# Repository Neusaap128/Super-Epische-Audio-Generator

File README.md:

**CubeIDEProject:** Deze bevat de code die we op de dev board geschreven hebben voor we overschakelde naar de PCB \
**FiltersWavFiles:** Bevat de C-code en de wav files van filters \
**KicadProject:** De technische schema's van onze PCB en hoe we alles hebben aangesloten aan elkaar \
**SEAG_F:** De implementatie op de STM32F722RC (wat we uitendelijk gebruikt hebben) \
**Super Epische Audio Generator:** Bevat Datasheet per onderdeel, PCB benodigheden, Tekst documenten voor Seminarie waar ook het eindverslag van alles staat

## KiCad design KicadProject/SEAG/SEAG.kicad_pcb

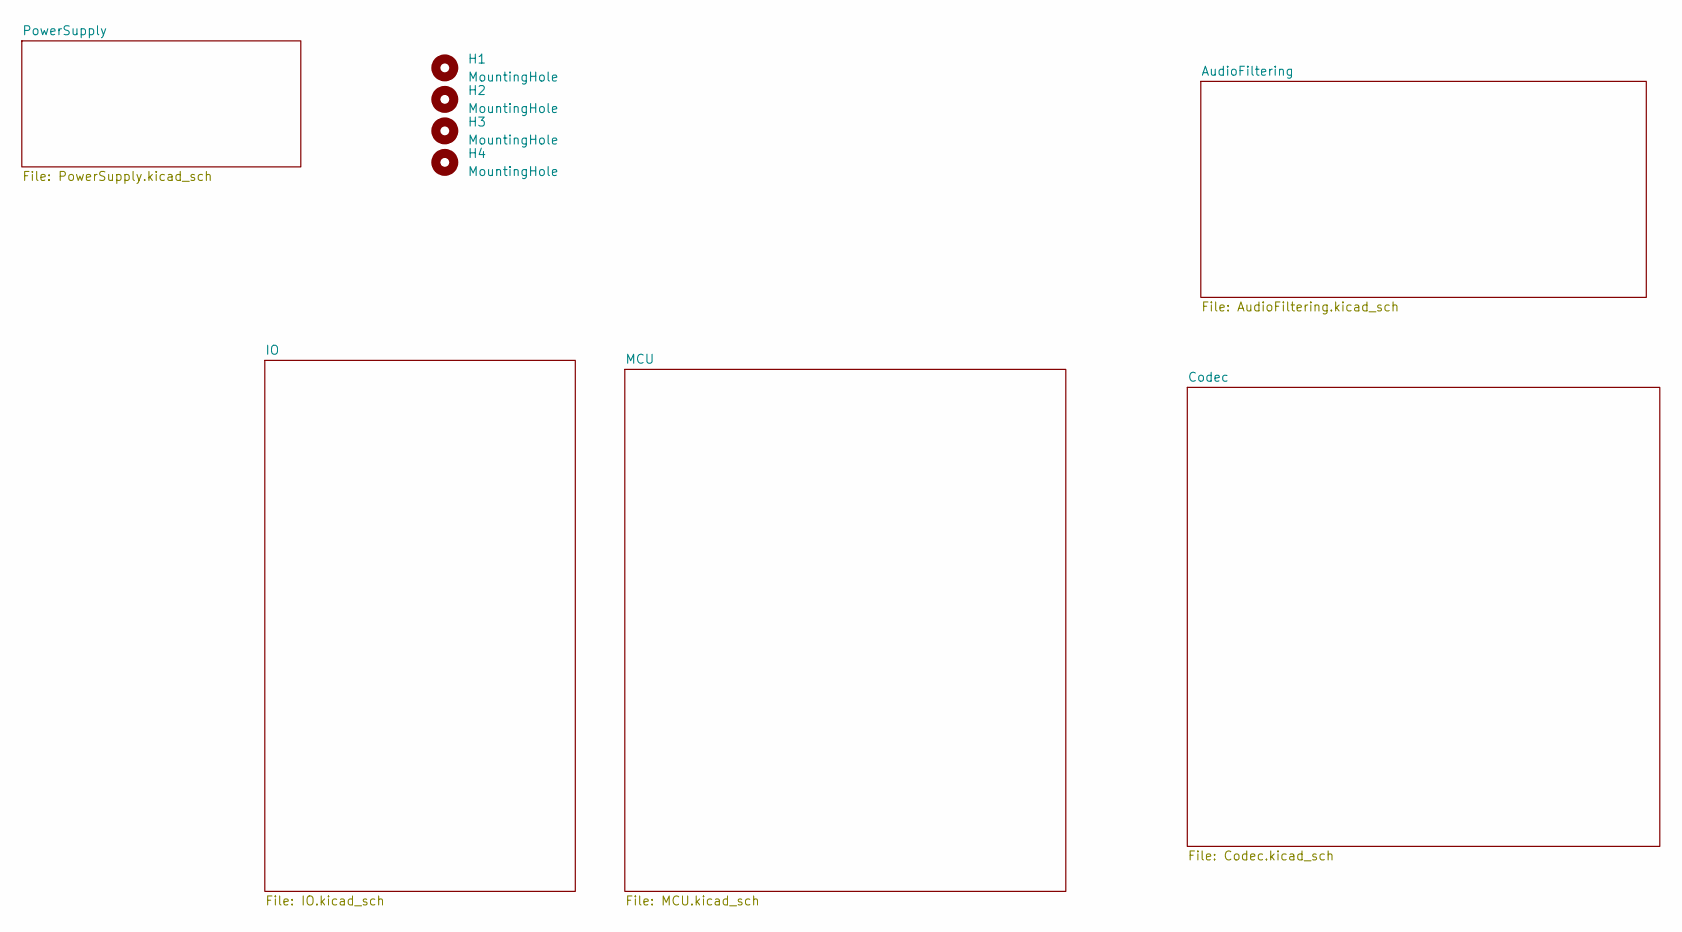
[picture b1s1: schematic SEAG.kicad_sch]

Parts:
H1, H2, H3, H4: MountingHole; MountingHole_3mm

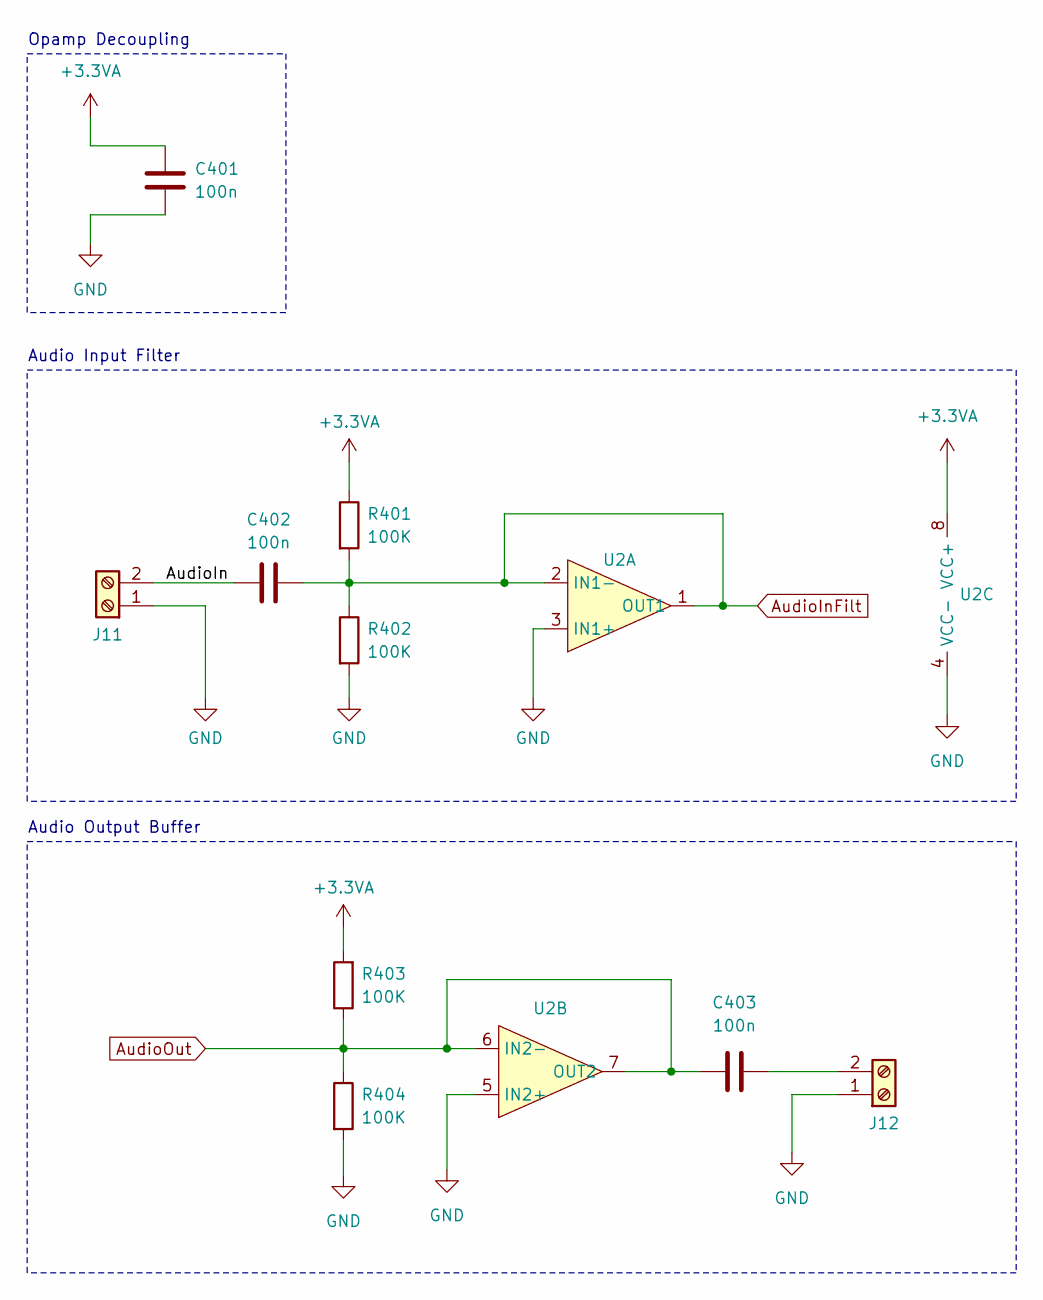
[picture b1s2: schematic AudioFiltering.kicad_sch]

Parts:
C401, C402, C403: 100n; C_0805_2012Metric
J11, J12: Screw_Terminal_01x02; TerminalBlock_Phoenix_MKDS-1,5-2_1x02_P5.00mm_Horizontal
R401, R402, R403, R404: 100K; R_0805_2012Metric
U2: SOIC127P600X175-8N

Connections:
+3.3VA: C401.1, R401.1, R403.2, U2.8 (VCC+); also elsewhere on the board
/AudioFiltering/AudioIn: C402.1, J11.2
AudioInFilt: C402.2, R401.2, R402.1, U2.1 (OUT1), U2.2 (IN1-); also elsewhere on the board
AudioOut: C403.1, R403.1, R404.1, U2.6 (IN2-), U2.7 (OUT2); also elsewhere on the board
GND: C401.2, J11.1, J12.1, R402.2, R404.2, U2.3 (IN1+), U2.4 (VCC-), U2.5 (IN2+); also elsewhere on the board
unnamed: C403.2, J12.2

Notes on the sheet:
Opamp Decoupling
Audio Input Filter
Audio Output Buffer

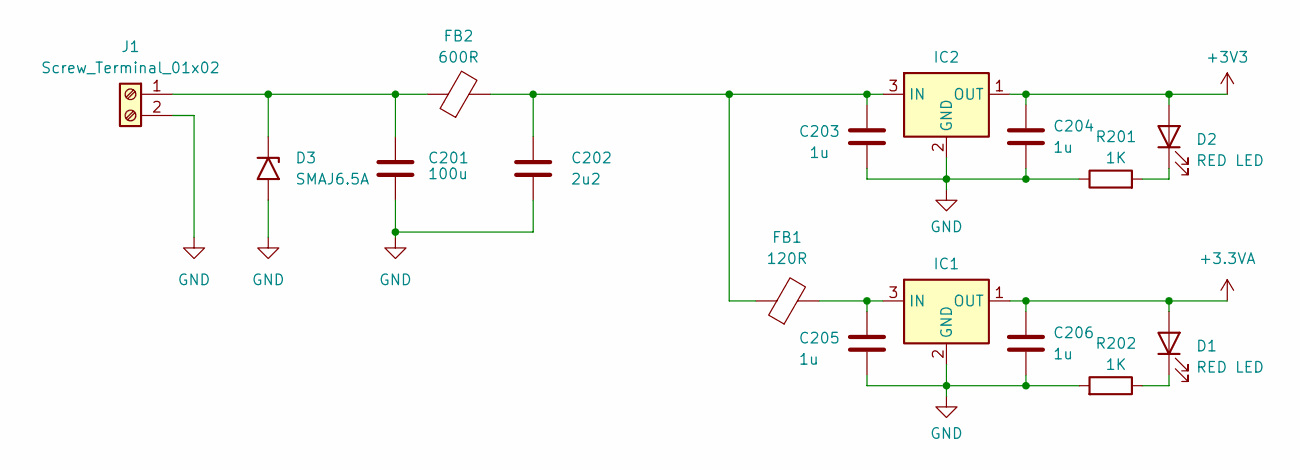
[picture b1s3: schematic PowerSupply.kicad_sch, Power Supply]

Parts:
C201: 100u; C_0805_2012Metric
C202: 2u2; C_0805_2012Metric
C203, C204, C205, C206: 1u; C_0805_2012Metric
D1, D2: RED LED; LED_0805_2012Metric
D3: SMAJ6.5A; D_SMA
FB1: 120R; L_0805_2012Metric
FB2: 600R; L_0805_2012Metric
IC1, IC2: AP736533YG13
J1: Screw_Terminal_01x02; TerminalBlock_Phoenix_MKDS-1,5-2_1x02_P5.00mm_Horizontal
R201, R202: 1K; R_0805_2012Metric

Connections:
+3.3VA: C206.1, D1.2 (A), IC1.1 (OUT); also elsewhere on the board
+3V3: C204.1, D2.2 (A), IC2.1 (OUT); also elsewhere on the board
GND: C201.2, C202.2, C203.2, C204.2, C205.2, C206.2, D3.2 (A2), IC1.2 (GND), IC1.4 (GND), IC2.2 (GND), IC2.4 (GND), J1.2, R201.1, R202.2; also elsewhere on the board
unnamed: D1.1 (K), R202.1
unnamed: D2.1 (K), R201.2
unnamed: C201.1, D3.1 (A1), FB2.1, J1.1
unnamed: C205.1, FB1.2, IC1.3 (IN)
unnamed: C202.1, C203.1, FB1.1, FB2.2, IC2.3 (IN)

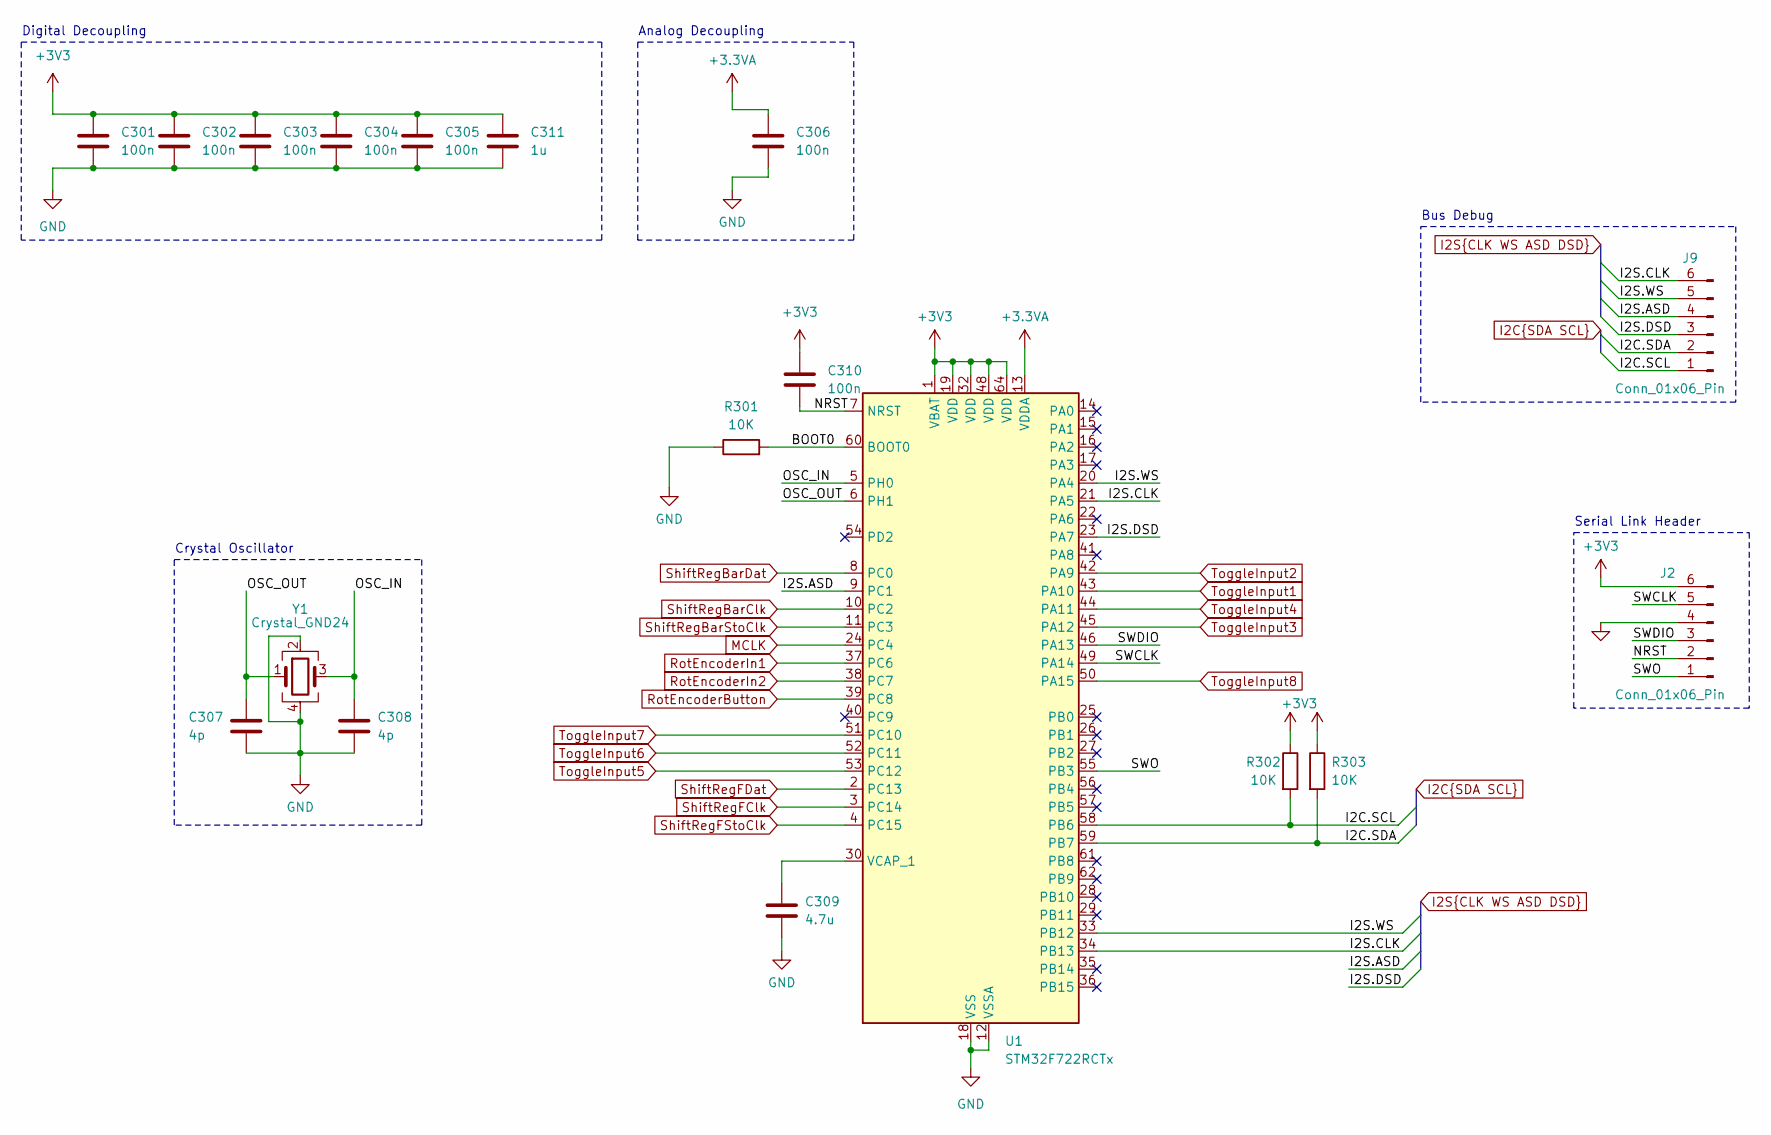
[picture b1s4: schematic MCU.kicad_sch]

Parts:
C301, C302, C303, C304, C305, C306, C310: 100n; C_0805_2012Metric
C307, C308: 4p; C_0805_2012Metric
C309: 4.7u; C_0805_2012Metric
C311: 1u; C_0805_2012Metric
J2, J9: Conn_01x06_Pin; PinHeader_1x06_P2.54mm_Vertical
R301, R302, R303: 10K; R_0805_2012Metric
U1: STM32F722RCTx; LQFP-64_10x10mm_P0.5mm
Y1: Crystal_GND24; FW2500025Z

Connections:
+3.3VA: C306.1, U1.13 (VDDA); also elsewhere on the board
+3V3: C301.1, C302.1, C303.1, C304.1, C305.1, C310.1, C311.1, J2.6, R302.1, R303.1, U1.1 (VBAT), U1.19 (VDD), U1.32 (VDD), U1.48 (VDD), U1.64 (VDD); also elsewhere on the board
/MCU/BOOT0: R301.2, U1.60 (BOOT0)
/MCU/NRST: C310.2, J2.2, U1.7 (NRST)
/MCU/OSC_IN: C308.1, U1.5 (PH0), Y1.3
/MCU/OSC_OUT: C307.1, U1.6 (PH1), Y1.1
/MCU/SWCLK: J2.5, U1.49 (PA14)
/MCU/SWDIO: J2.3, U1.46 (PA13)
/MCU/SWO: J2.1, U1.55 (PB3)
GND: C301.2, C302.2, C303.2, C304.2, C305.2, C306.2, C307.2, C308.2, C309.2, C311.2, J2.4, R301.1, U1.12 (VSSA), U1.18 (VSS), U1.31 (VSS), U1.47 (VSS), U1.63 (VSS), Y1.2, Y1.4; also elsewhere on the board
I2C.SCL: J9.1, R302.2, U1.58 (PB6); also elsewhere on the board
I2C.SDA: J9.2, R303.2, U1.59 (PB7); also elsewhere on the board
I2S.ASD: J9.4, U1.9 (PC1); also elsewhere on the board
I2S.CLK: J9.6, U1.21 (PA5), U1.34 (PB13); also elsewhere on the board
I2S.DSD: J9.3, U1.23 (PA7); also elsewhere on the board
I2S.WS: J9.5, U1.20 (PA4), U1.33 (PB12); also elsewhere on the board
MCLK: U1.24 (PC4); also elsewhere on the board
unnamed: C309.1, U1.30 (VCAP_1)
RotEncoderButton: U1.39 (PC8); also elsewhere on the board
RotEncoderIn1: U1.37 (PC6); also elsewhere on the board
RotEncoderIn2: U1.38 (PC7); also elsewhere on the board
ShiftRegBarClk: U1.10 (PC2); also elsewhere on the board
ShiftRegBarDat: U1.8 (PC0); also elsewhere on the board
ShiftRegBarStoClk: U1.11 (PC3); also elsewhere on the board
ShiftRegFClk: U1.3 (PC14); also elsewhere on the board
ShiftRegFDat: U1.2 (PC13); also elsewhere on the board
ShiftRegFStoClk: U1.4 (PC15); also elsewhere on the board
ToggleInput1: U1.43 (PA10); also elsewhere on the board
ToggleInput2: U1.42 (PA9); also elsewhere on the board
ToggleInput3: U1.45 (PA12); also elsewhere on the board
ToggleInput4: U1.44 (PA11); also elsewhere on the board
ToggleInput5: U1.53 (PC12); also elsewhere on the board
ToggleInput6: U1.52 (PC11); also elsewhere on the board
ToggleInput7: U1.51 (PC10); also elsewhere on the board
ToggleInput8: U1.50 (PA15); also elsewhere on the board

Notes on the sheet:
Serial Link Header
Crystal Oscillator
Digital Decoupling
Analog Decoupling
Bus Debug

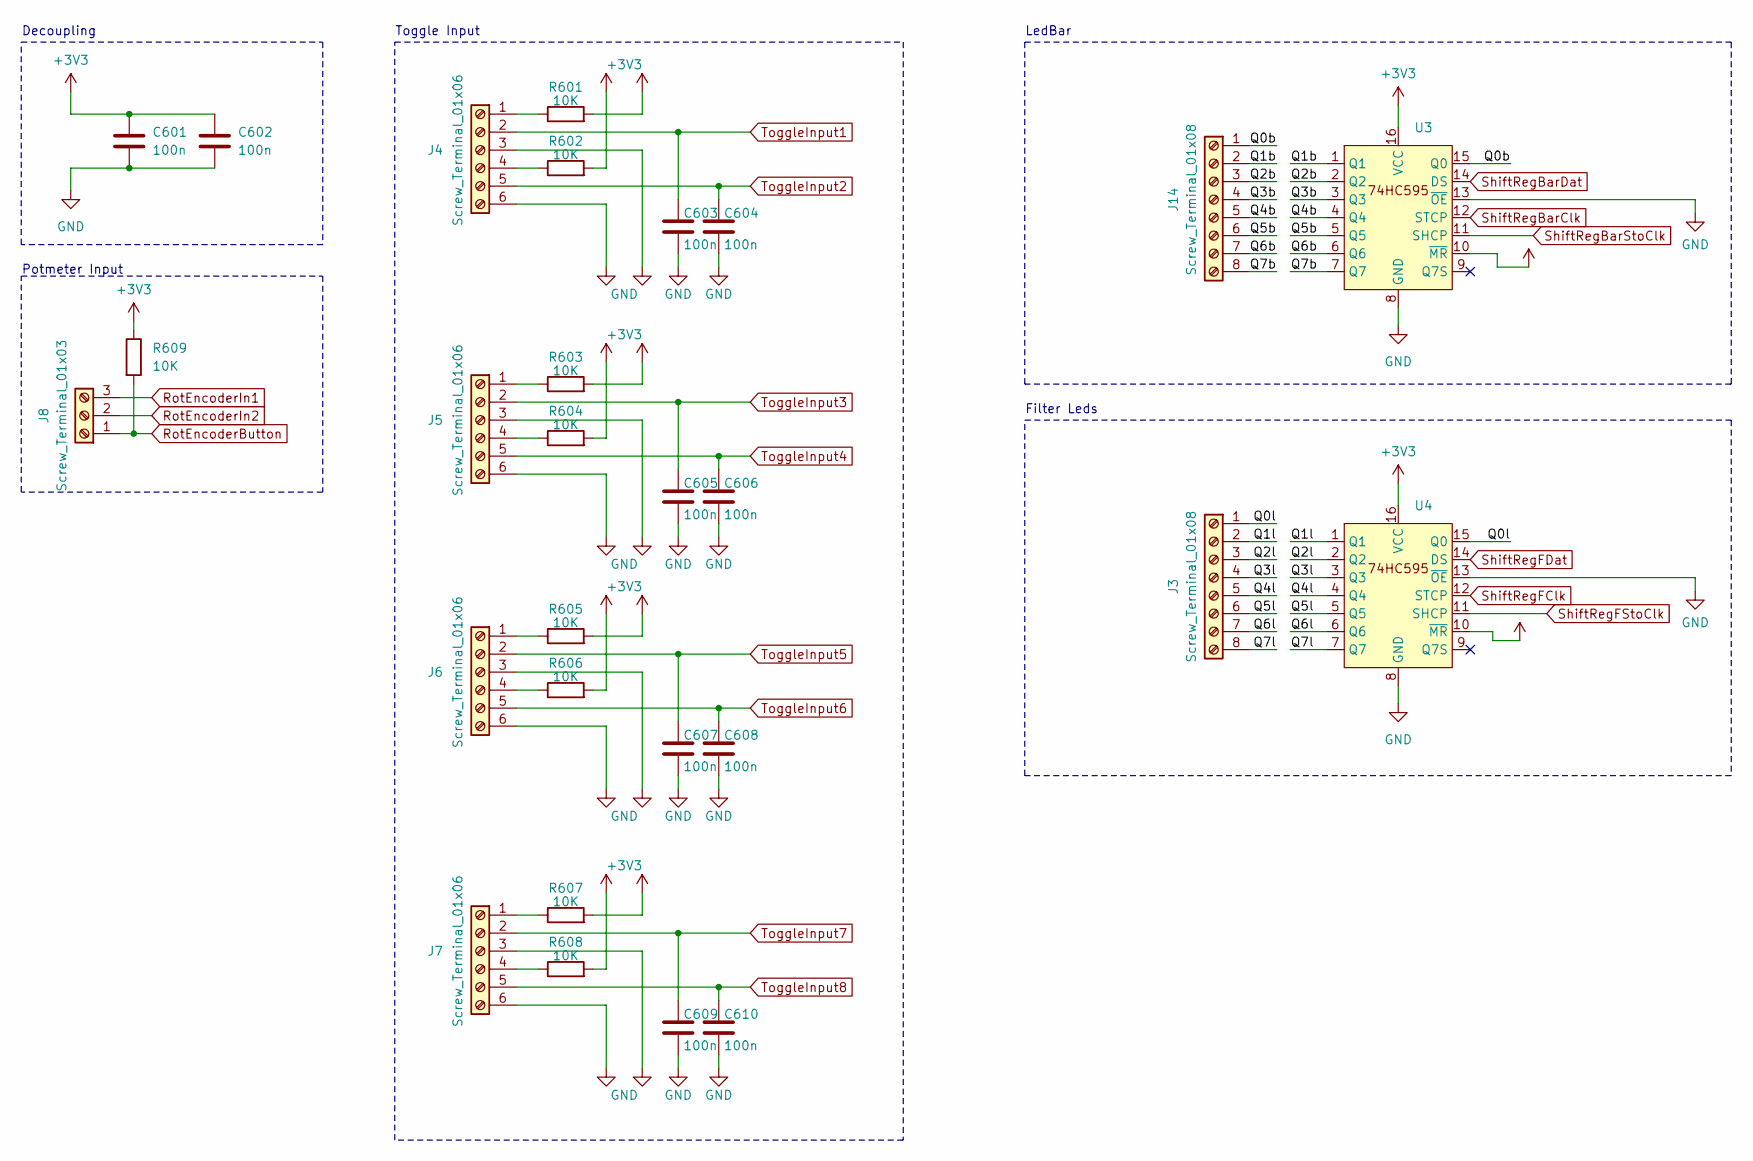
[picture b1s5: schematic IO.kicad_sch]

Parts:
C601, C602, C603, C604, C605, C606, C607, C608, C609, C610: 100n; C_0805_2012Metric
J3, J14: Screw_Terminal_01x08; 1725711
J4, J5, J6, J7: Screw_Terminal_01x06; 1725698
J8: Screw_Terminal_01x03; 2828343
R601, R602, R603, R604, R605, R606, R607, R608, R609: 10K; R_0805_2012Metric
U3, U4: 74HC595DQ100118

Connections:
+3V3: C601.1, C602.1, R601.2, R602.2, R603.2, R604.2, R605.2, R606.2, R607.2, R608.2, R609.1, U3.10 (~MR), U3.16 (VCC), U4.10 (~MR), U4.16 (VCC); also elsewhere on the board
/IO/Q0b: J14.1, U3.15 (Q0)
/IO/Q0l: J3.1, U4.15 (Q0)
/IO/Q1b: J14.2, U3.1 (Q1)
/IO/Q1l: J3.2, U4.1 (Q1)
/IO/Q2b: J14.3, U3.2 (Q2)
/IO/Q2l: J3.3, U4.2 (Q2)
/IO/Q3b: J14.4, U3.3 (Q3)
/IO/Q3l: J3.4, U4.3 (Q3)
/IO/Q4b: J14.5, U3.4 (Q4)
/IO/Q4l: J3.5, U4.4 (Q4)
/IO/Q5b: J14.6, U3.5 (Q5)
/IO/Q5l: J3.6, U4.5 (Q5)
/IO/Q6b: J14.7, U3.6 (Q6)
/IO/Q6l: J3.7, U4.6 (Q6)
/IO/Q7b: J14.8, U3.7 (Q7)
/IO/Q7l: J3.8, U4.7 (Q7)
GND: C601.2, C602.2, C603.2, C604.2, C605.2, C606.2, C607.2, C608.2, C609.2, C610.2, J4.3, J4.6, J5.3, J5.6, J6.3, J6.6, J7.3, J7.6, U3.8 (GND), U3.13 (~OE), U4.8 (GND), U4.13 (~OE); also elsewhere on the board
unnamed: J4.1, R601.1
unnamed: J4.4, R602.1
unnamed: J5.1, R603.1
unnamed: J5.4, R604.1
unnamed: J6.1, R605.1
unnamed: J6.4, R606.1
unnamed: J7.1, R607.1
unnamed: J7.4, R608.1
RotEncoderButton: J8.1, R609.2; also elsewhere on the board
RotEncoderIn1: J8.3; also elsewhere on the board
RotEncoderIn2: J8.2; also elsewhere on the board
ShiftRegBarClk: U3.12 (STCP); also elsewhere on the board
ShiftRegBarDat: U3.14 (DS); also elsewhere on the board
ShiftRegBarStoClk: U3.11 (SHCP); also elsewhere on the board
ShiftRegFClk: U4.12 (STCP); also elsewhere on the board
ShiftRegFDat: U4.14 (DS); also elsewhere on the board
ShiftRegFStoClk: U4.11 (SHCP); also elsewhere on the board
ToggleInput1: C603.1, J4.2; also elsewhere on the board
ToggleInput2: C604.1, J4.5; also elsewhere on the board
ToggleInput3: C605.1, J5.2; also elsewhere on the board
ToggleInput4: C606.1, J5.5; also elsewhere on the board
ToggleInput5: C607.1, J6.2; also elsewhere on the board
ToggleInput6: C608.1, J6.5; also elsewhere on the board
ToggleInput7: C609.1, J7.2; also elsewhere on the board
ToggleInput8: C610.1, J7.5; also elsewhere on the board

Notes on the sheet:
Filter Leds
LedBar
Decoupling
Potmeter Input
Toggle Input

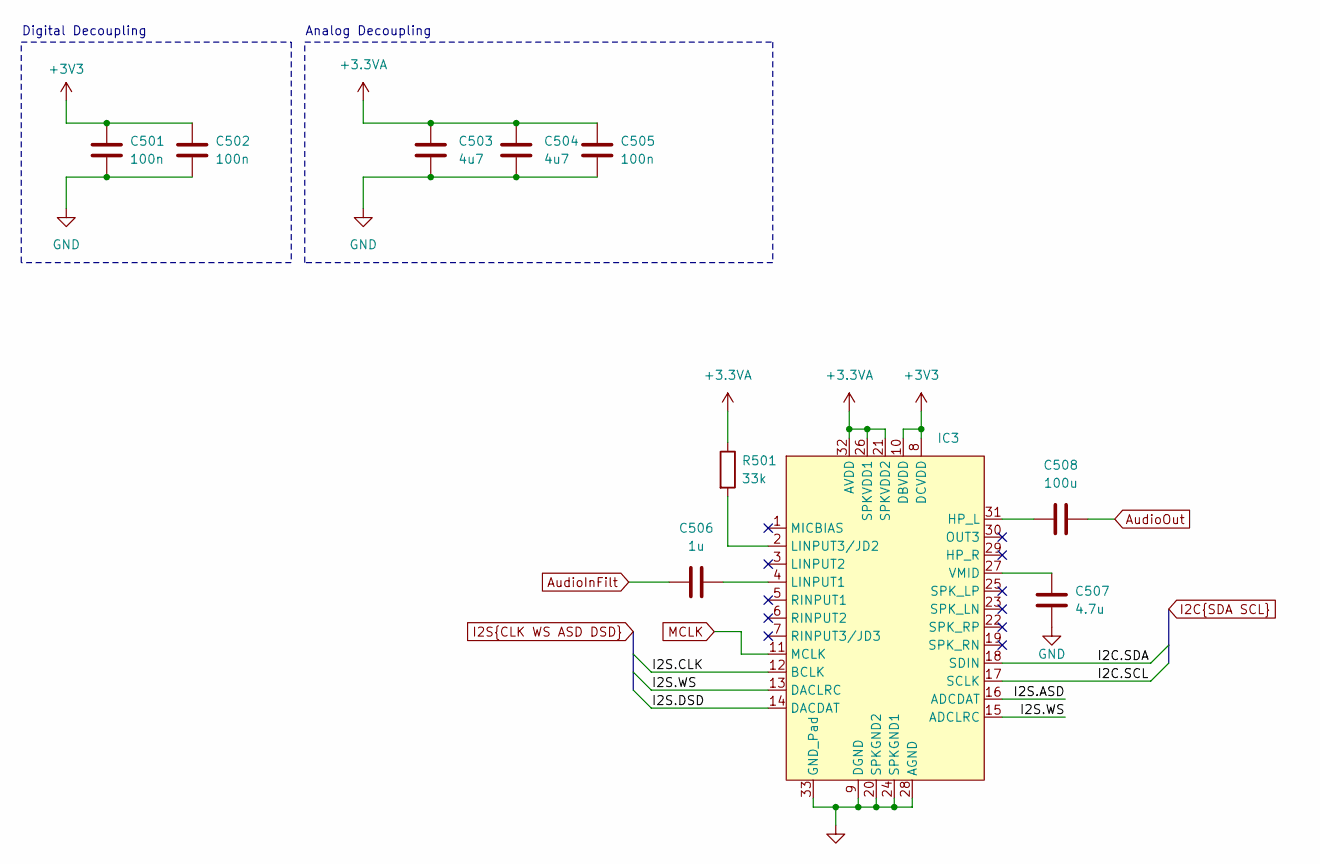
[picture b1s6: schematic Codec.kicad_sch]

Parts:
C501, C502, C505: 100n; C_0805_2012Metric
C503, C504: 4u7; C_0805_2012Metric
C506: 1u; C_0805_2012Metric
C507: 4.7u; C_0805_2012Metric
C508: 100u; C_0805_2012Metric
IC3: QFN50P500X500X100-33N
R501: 33k; R_0805_2012Metric

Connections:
+3.3VA: C503.1, C504.1, C505.1, IC3.21 (SPKVDD2), IC3.26 (SPKVDD1), IC3.32 (AVDD), R501.1; also elsewhere on the board
+3V3: C501.1, C502.1, IC3.8 (DCVDD), IC3.10 (DBVDD); also elsewhere on the board
AudioInFilt: C506.1; also elsewhere on the board
AudioOut: C508.2; also elsewhere on the board
GND: C501.2, C502.2, C503.2, C504.2, C505.2, C507.2, IC3.9 (DGND), IC3.20 (SPKGND2), IC3.24 (SPKGND1), IC3.28 (AGND), IC3.33 (GND_Pad); also elsewhere on the board
I2C.SCL: IC3.17 (SCLK); also elsewhere on the board
I2C.SDA: IC3.18 (SDIN); also elsewhere on the board
I2S.ASD: IC3.16 (ADCDAT); also elsewhere on the board
I2S.CLK: IC3.12 (BCLK); also elsewhere on the board
I2S.DSD: IC3.14 (DACDAT); also elsewhere on the board
I2S.WS: IC3.13 (DACLRC), IC3.15 (ADCLRC); also elsewhere on the board
MCLK: IC3.11 (MCLK); also elsewhere on the board
unnamed: C508.1, IC3.31 (HP_L)
unnamed: C506.2, IC3.4 (LINPUT1)
unnamed: IC3.2 (LINPUT3/JD2), R501.2
unnamed: C507.1, IC3.27 (VMID)

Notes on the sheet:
Analog Decoupling
Digital Decoupling

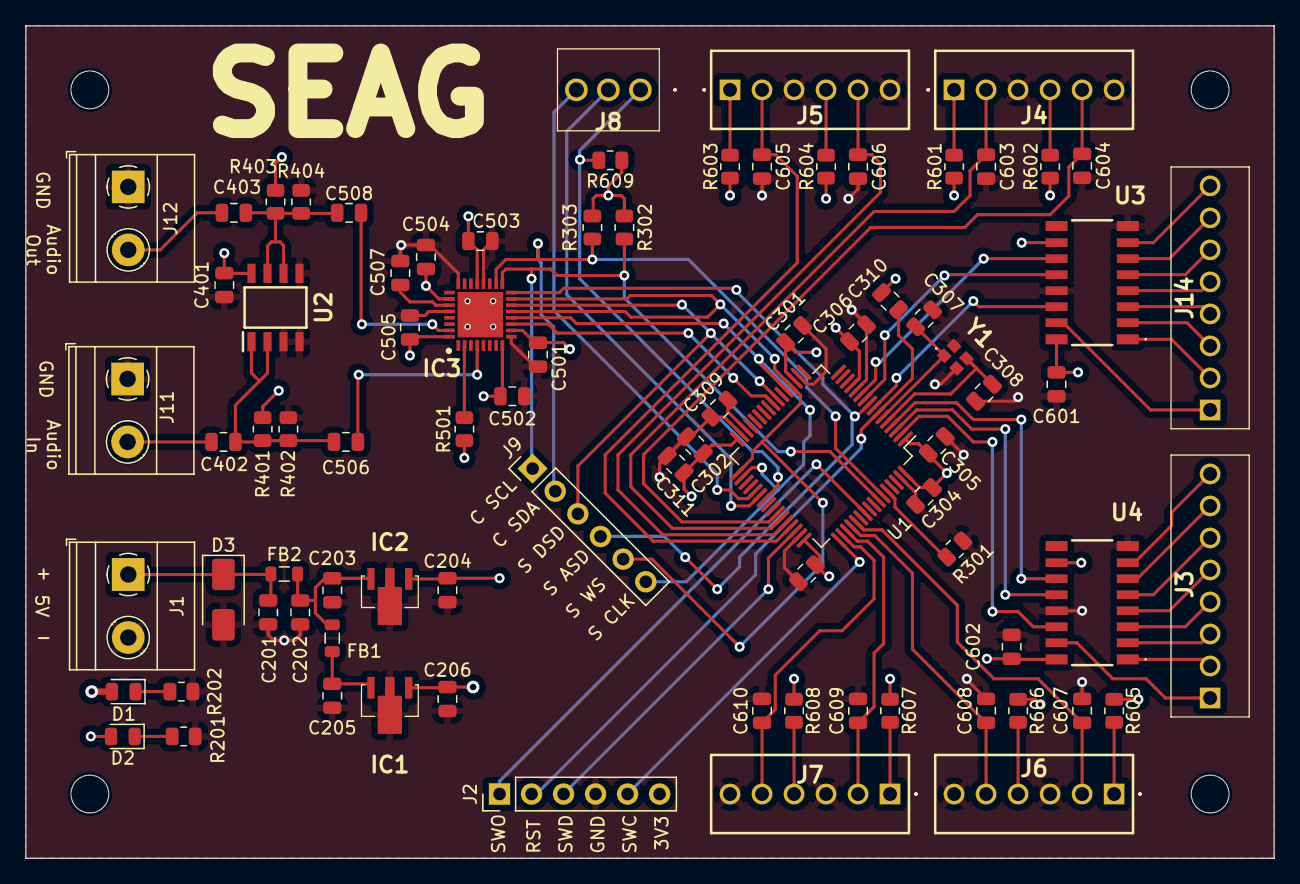
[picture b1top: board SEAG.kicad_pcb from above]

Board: 4 copper layers, 99.1 x 66.1 mm, 86 parts (0 on the bottom side), 72 nets.

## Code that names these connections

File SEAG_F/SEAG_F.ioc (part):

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Mcu.Name=STM32F722R(C-E)Tx
Mcu.Package=LQFP64
Mcu.UserName=STM32F722RCTx
PA10.GPIOParameters=GPIO_Label
PA10.GPIO_Label=ToggleInput3
PA10.Signal=GPIO_Input
PA11.GPIOParameters=GPIO_Label
PA11.GPIO_Label=ToggleInput2
PA11.Signal=GPIO_Input
PA12.GPIOParameters=GPIO_Label
PA12.GPIO_Label=ToggleInput1
PA12.Signal=GPIO_Input
PA13.Mode=Serial_Wire
PA13.Signal=SYS_JTMS-SWDIO
PA14.Mode=Serial_Wire
PA14.Signal=SYS_JTCK-SWCLK
PA15.GPIOParameters=GPIO_Label
PA15.GPIO_Label=ToggleInput8
PA15.Signal=GPIO_Input
PA4.Mode=Half_Duplex_Master
PA4.Signal=I2S1_WS
PA5.Mode=Half_Duplex_Master
PA5.Signal=I2S1_CK
PA7.Mode=Half_Duplex_Master
PA7.Signal=I2S1_SD
PA9.GPIOParameters=GPIO_Label
PA9.GPIO_Label=ToggleInput4
PA9.Signal=GPIO_Input
PB12.Mode=Half_Duplex_Slave
PB12.Signal=I2S2_WS
PB13.Mode=Half_Duplex_Slave
PB13.Signal=I2S2_CK
PB6.Mode=I2C
PB6.Signal=I2C1_SCL
PB7.Mode=I2C
PB7.Signal=I2C1_SDA
PC0.GPIOParameters=GPIO_Label
PC0.GPIO_Label=ShiftRegLBarDat
PC0.Signal=GPIO_Output
PC1.Mode=Half_Duplex_Slave
PC1.Signal=I2S2_SD
PC10.GPIOParameters=GPIO_Label
PC10.GPIO_Label=ToggleInput7
PC10.Signal=GPIO_Input
PC11.GPIOParameters=GPIO_Label
PC11.GPIO_Label=ToggleInput6
PC11.Signal=GPIO_Input
PC12.GPIOParameters=GPIO_Label
PC12.GPIO_Label=ToggleInput5
PC12.Signal=GPIO_Input
PC13.GPIOParameters=GPIO_Label
PC13.GPIO_Label=ShiftRegFDat
PC13.Signal=GPIO_Output
PC14-OSC32_IN.GPIOParameters=GPIO_Label
PC14-OSC32_IN.GPIO_Label=ShiftRegFStoClk
PC14-OSC32_IN.Signal=GPIO_Output
PC15-OSC32_OUT.GPIOParameters=GPIO_Label
PC15-OSC32_OUT.GPIO_Label=ShiftRegFClk
PC15-OSC32_OUT.Signal=GPIO_Output
PC2.GPIOParameters=GPIO_Label
PC2.GPIO_Label=ShiftRegLBarStoClk
PC2.Signal=GPIO_Output
PC3.GPIOParameters=GPIO_Label
PC3.GPIO_Label=ShiftRegLBarClk
PC3.Signal=GPIO_Output
PC4.Mode=Master_Clock_Activated
PC4.Signal=I2S1_MCK
PC6.GPIOParameters=GPIO_Label
PC6.GPIO_Label=RotEncoderInA
PC6.Signal=GPXTI6
PC7.GPIOParameters=GPIO_Label,GPIO_ModeDefaultEXTI
PC7.GPIO_Label=RotEncoderInB
PC7.GPIO_ModeDefaultEXTI=GPIO_MODE_IT_RISING_FALLING
PC7.Signal=GPXTI7
PC8.GPIOParameters=GPIO_Label,GPIO_ModeDefaultEXTI
PC8.GPIO_Label=RotEncoderButton
PC8.GPIO_ModeDefaultEXTI=GPIO_MODE_IT_RISING
PC8.Signal=GPXTI8
PH0-OSC_IN.Mode=HSE-External-Oscillator
PH0-OSC_IN.Signal=RCC_OSC_IN
PH1-OSC_OUT.Mode=HSE-External-Oscillator
PH1-OSC_OUT.Signal=RCC_OSC_OUT
RCC.HSE_VALUE=25000000
RCC.SYSCLKFreq_VALUE=216000000
RCC.SYSCLKSource=RCC_SYSCLKSOURCE_PLLCLK
board=custom

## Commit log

2024-02-21 Added Cube project, made blinking LED
2024-02-22 configured ADC0 pin
2024-02-25 Configured DAC, ADC, TIM. Added preliminary files
2024-02-28 To be sure project is up to date in class
2024-02-29 de taak van profesionele competenties toegevoegd met deadline 6/3 added SEAG.md
2024-02-29 incoming sample, directly placed on DAC
2024-02-29 idk random zever
2024-02-29 added git ignore with .json
2024-02-29 Added DMA support, ADC works, DAC needs work. Added schedule to obsidian under folder 'Seminaries'
2024-02-29 Tried some stuff with ioc file, DAC DMA doesnt work
2024-03-02 Added datasheets and footprint reference to obsidian. Drew schematic for MCU decoupling and crystal circuitry
2024-03-02 Added power supply and serial link header to PCB schematic
2024-03-05 Added 'AudioFiltering' and 'Codec' sheets to PCB schematic, started PCB layout with decouple caps and MCU. The codec in sheet 'Codec' is wrong, placed for testing
2024-03-07 seminaries documentatie: excel planning, temp bom lijst in foot prints en stakeholder analyse
2024-03-07 Added ESD protection, extra filtering with ferrite bead
2024-03-08 Small note in PCB Design, about planes on PCB
2024-03-17 Declaration of the codec and its registers
2024-03-21 write reg function modified to send 2 byte's
2024-03-23 toevoeging van io
2024-03-26 i2S clock gefixt
2024-03-31 Finished PCB, stil uncertain about couple things
2024-04-01 PCB rev 2
2024-04-01 geen idee
2024-04-01 on pcb
2024-04-01 Added rotary encoder screw terminal
2024-04-02 gezevert aan pcb
2024-04-09 Slight PCB changes
2024-04-17 Added header
2024-04-20 Generated gerber files, also ordered PCB
2024-04-24 IO files
2024-04-24 Small changes to IO code
2024-04-24 Fixed errors in IO files
2024-04-30 Made stm32F722 project. Added reverb filter
2024-05-06 toevoeging rot en aanpassing io file naar rot
2024-05-06 Rotary Encoder struct
2024-05-07 new register configuration based on the sparkfun library
2024-05-12 code for pcb
2024-05-13 Changed codec write register function, data bit to reg addr
2024-05-13 Added Filters.h & Filters.c
2024-05-15 Sent 0 to right channel in process buffer. Set index 0 of selected filter with toggle (not tested)
2024-05-16 turned of loopback in codec, shiftbuffer aint working
2024-05-16 Documentatie
2024-05-17 Switched I²S and DMA to 16 bit
2024-05-18 added low pass filter & distortion, both not working
2024-05-19 Working reverb filter, added low-high pass
2024-05-20 Added flanger, chorus (both kinda scuffed), added methods to change filter level. added Filter struct to represent a filter with its methods
2024-05-21 final changes to IO
2024-05-22 paar comentaar aan geven
2024-05-22 eerste deel commentaar
2024-05-22 Added comments to DSP.c
2024-05-23 toevoeging wav files, datasheet io, 2D tekeningen
2024-05-24 code updqted
2024-05-25 Bolt titles in README
2024-05-25 new line in README
2024-05-25 Removed documentatie from readme
